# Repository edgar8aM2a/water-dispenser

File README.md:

# Automatic water dispenser -MEGA

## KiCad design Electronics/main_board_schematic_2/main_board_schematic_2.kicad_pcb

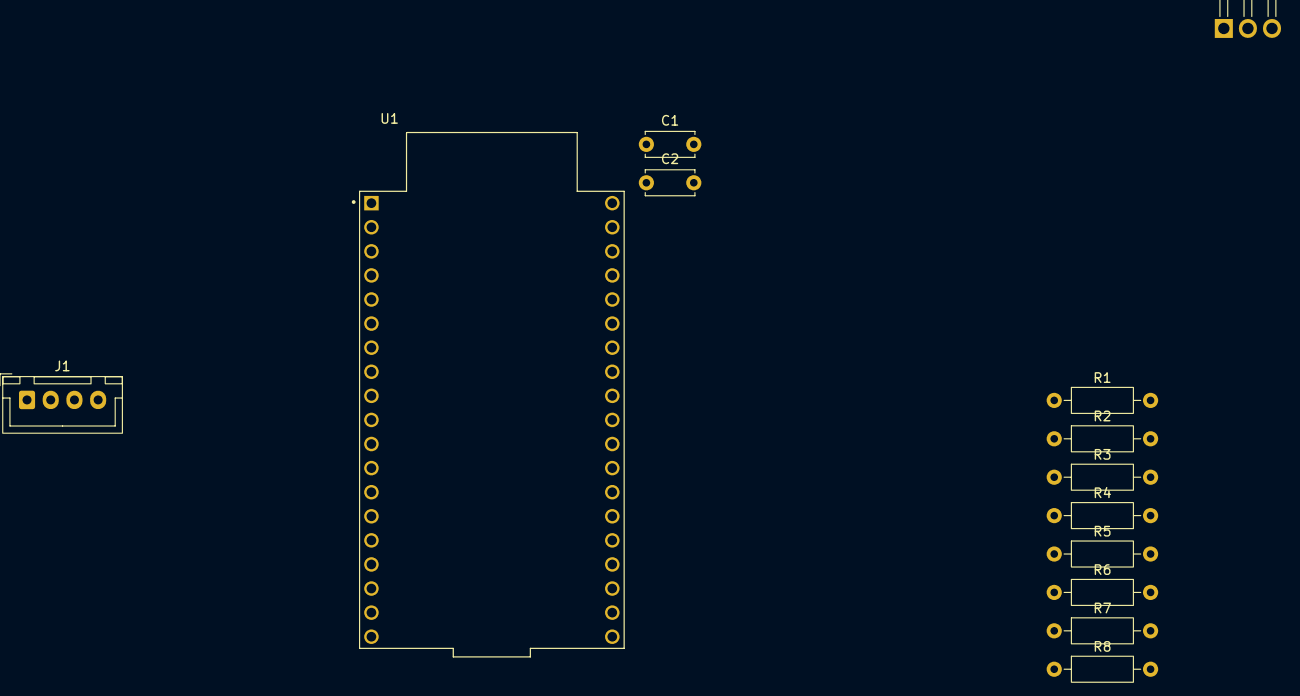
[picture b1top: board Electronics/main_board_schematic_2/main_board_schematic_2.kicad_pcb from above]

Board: 2 copper layers, 13 parts (0 on the bottom side), 4 nets, no tracks yet.

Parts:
C1: 0.1uf; C_Disc_D5.0mm_W2.5mm_P5.00mm
C2: 0.33uf; C_Disc_D5.0mm_W2.5mm_P5.00mm
J1: Conn_01x04_Pin; JST_XH_B4B-XH-A_1x04_P2.50mm_Vertical
R1, R2, R3, R4, R5, R6, R7, R8: 100; R_Axial_DIN0207_L6.3mm_D2.5mm_P10.16mm_Horizontal
U1: DEVKIT_V1_ESP32-WROOM-32; MODULE_DEVKIT_V1_ESP32-WROOM-32
U2: L7805; TO-220F-3_Horizontal_TabDown

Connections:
+5V: C1.1, U1.19 (EXT_5V), U2.3 (OUT)
+12V: C2.1, U2.1 (IN)
/5v: J1.2, R1.1, R2.1, R3.1, R4.1, R5.1, R6.1, R7.1, R8.1
GND: C1.2, C2.2, U1.15 (IO13), U2.2 (GND)

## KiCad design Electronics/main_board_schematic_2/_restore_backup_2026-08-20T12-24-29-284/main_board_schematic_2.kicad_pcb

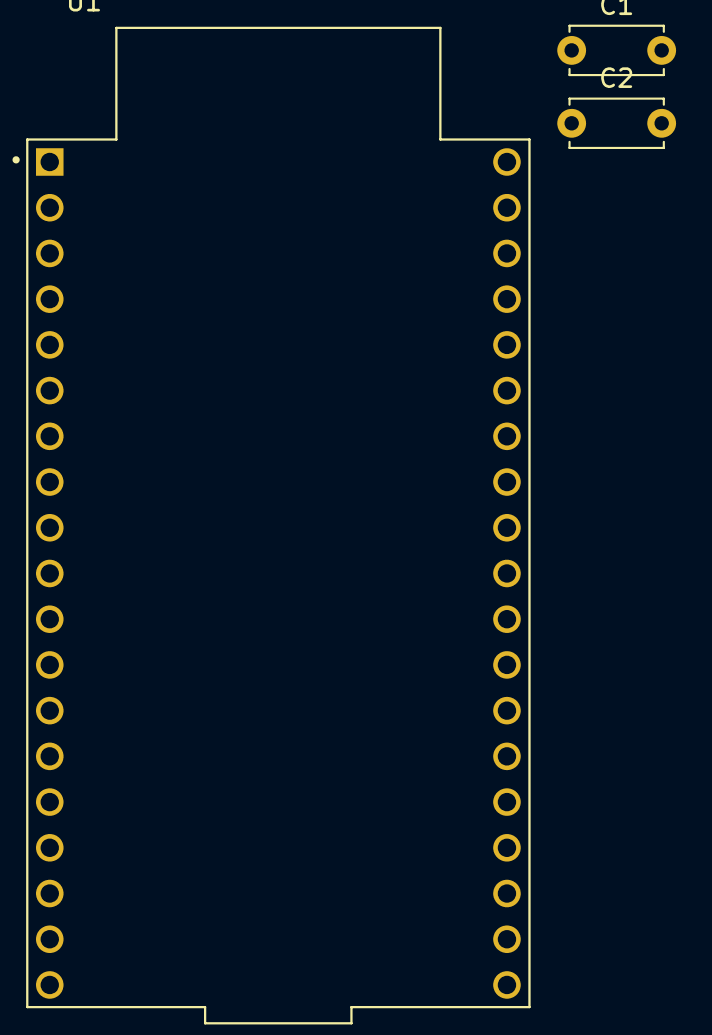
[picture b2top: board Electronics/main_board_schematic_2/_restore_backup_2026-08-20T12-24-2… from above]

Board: 2 copper layers, 3 parts (0 on the bottom side), 2 nets, no tracks yet.

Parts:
C1: 0.1uf; C_Disc_D5.0mm_W2.5mm_P5.00mm
C2: 0.33uf; C_Disc_D5.0mm_W2.5mm_P5.00mm
U1: DEVKIT_V1_ESP32-WROOM-32; MODULE_DEVKIT_V1_ESP32-WROOM-32

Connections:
+5V: C1.1, U1.19 (EXT_5V)
GND: C1.2, C2.2, U1.15 (IO13)

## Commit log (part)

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2025-04-24 Initial commit: setup project structure
2025-05-26 project imported from pc to RSBPi
2025-11-16 Primer commit desdesde Raspberry Pi
2025-11-16 movi todo a la carpeta unitTest
2025-11-19 modify buttons_test
2025-11-23 Migrate to arduino
2025-11-26 Hardware integration test COMPLETED
2026-01-16 test_buttons|PASSED
2026-02-19 v3 pre test
    se encontraron bugs en electronica, pero la logica del codigo esta lista, siempre que no se tengan que hacer ajsutes en software para solucionar la electronica
